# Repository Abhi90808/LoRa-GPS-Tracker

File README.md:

# LoRa GPS Tracker

A custom PCB GPS tracker using LoRa wireless communication for long-range, low-power asset tracking. Designed in KiCad 8, combining a GPS module and LoRa transceiver for remote location reporting.

---

## Features
- LoRa long-range wireless (up to 10km line-of-sight)
- GPS module integration (NEO-6M or compatible)
- Ultra-low power design for battery operation
- SMA or u.FL antenna connector
- Compatible with LoRaWAN / peer-to-peer

## Specifications

| Parameter | Value |
|-----------|-------|
| LoRa Module | Ra-02 / RFM95W (SX1278) |
| GPS Module | NEO-6M / NEO-8M |
| Frequency | 433MHz / 868MHz / 915MHz |
| Range | Up to 10km (line of sight) |
| Supply Voltage | 3.3V |
| Interface | SPI (LoRa), UART (GPS) |
| PCB Layers | 2 |
| Designed With | KiCad 8 |

## Project Structure

```
├── Schematic/       # KiCad schematic (.kicad_sch, PDF)
├── PCB/             # PCB layout (.kicad_pcb, .kicad_pro)
├── Gerbers/         # Fabrication files
├── BOM/             # Bill of materials (CSV)
├── 3D/              # 3D model (.step)
└── Images/          # PCB renders and schematic screenshots
```

## How It Works

The GPS module sends NMEA sentences via UART to the MCU. The MCU parses the latitude/longitude and transmits it as a LoRa packet. A receiver node (another LoRa module or a LoRaWAN gateway) picks up the packet and logs or displays the location.

## Bill of Materials (Summary)

| Component | Value | Qty |
|-----------|-------|-----|
| LoRa Module | Ra-02 / RFM95W | 1 |
| GPS Module | NEO-6M | 1 |
| MCU | ATmega328p / STM32 | 1 |
| Voltage Regulator | AMS1117-3.3V | 1 |
| Antenna Connector | SMA / u.FL | 1 |

## Fabrication

Gerber files are in `/Gerbers`, ready for JLCPCB, PCBWay, or similar.

## License

This project is licensed under the [CERN Open Hardware Licence Version 2 - Strongly Reciprocal (CERN OHL-S v2)](https://ohwr.org/cern_ohl_s_v2.txt).

## Author

**Abhi90808** — [GitHub Profile](https://github.com/Abhi90808)

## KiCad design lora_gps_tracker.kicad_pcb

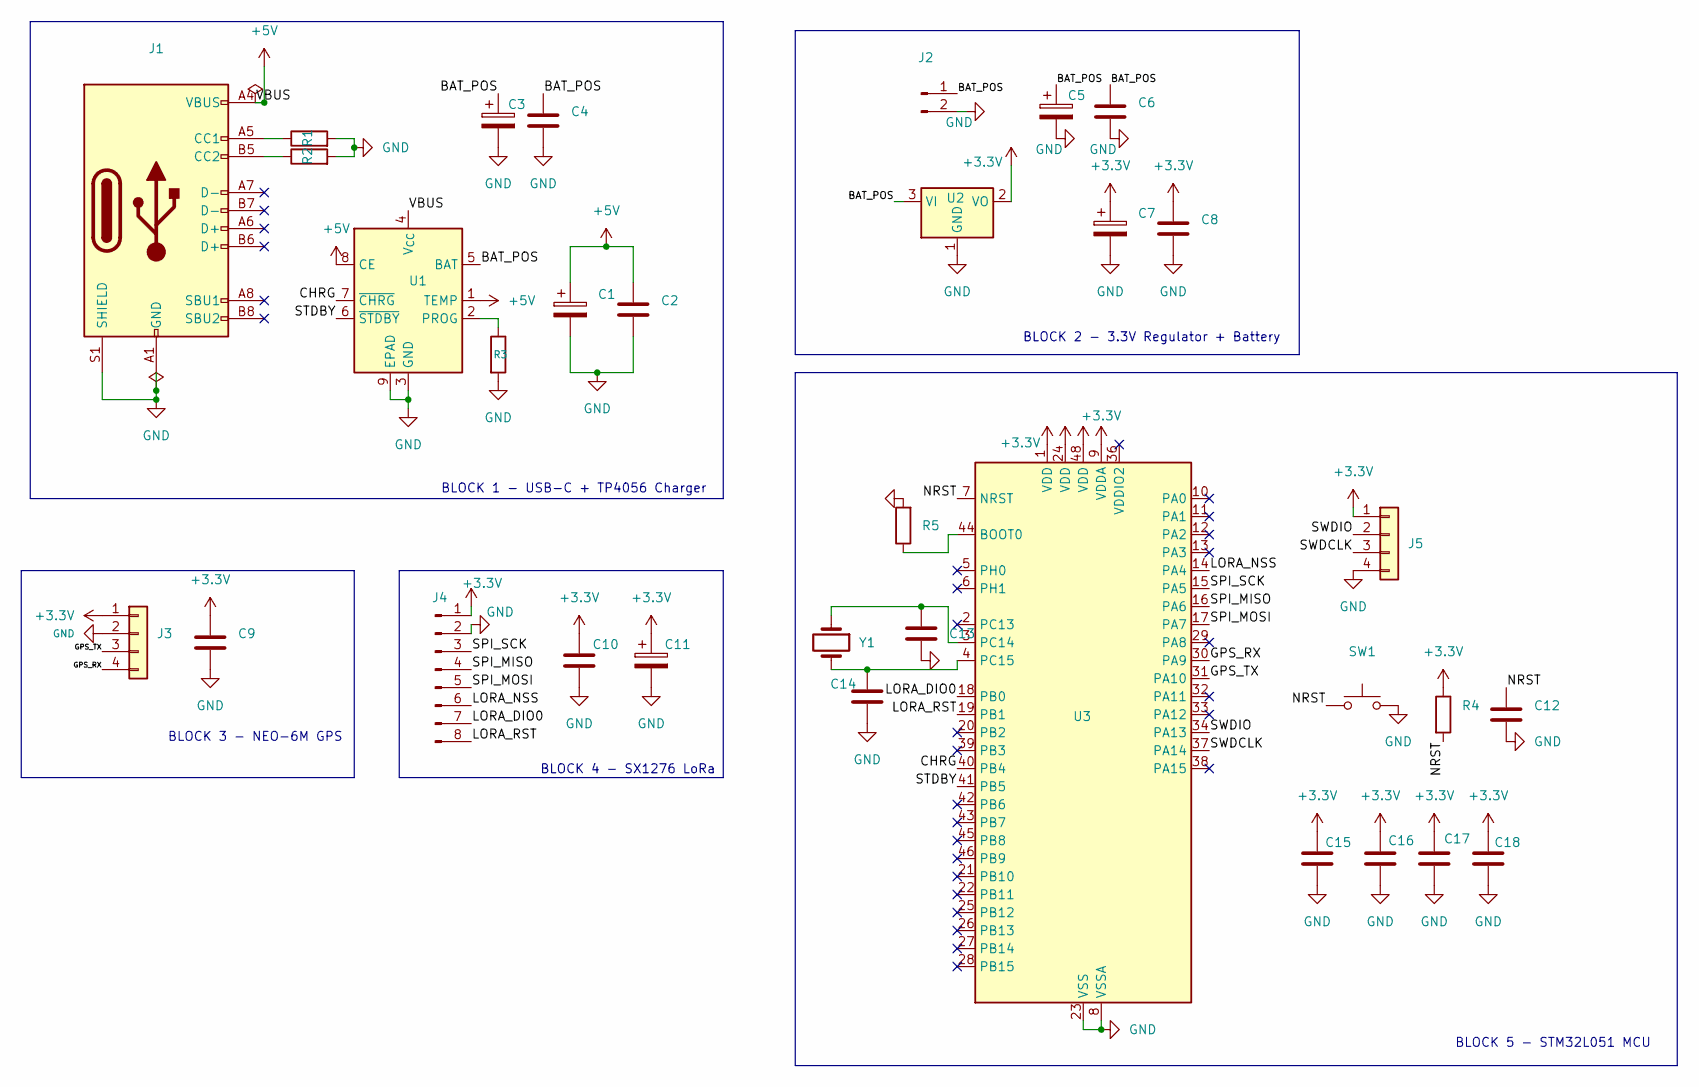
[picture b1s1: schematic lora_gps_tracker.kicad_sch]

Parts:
C1, C3, C5, C7, C11: 10uf; C_0805_2012Metric
C2, C4, C6, C8, C9, C10, C12, C15: 100nf; C_0402_1005Metric
C13, C14, C16, C17, C18: 12pf; C_0402_1005Metric
J1: USB_C; USB_C_Receptacle_XKB_U262-16XN-4BVC11
J2: BATTERY; PinHeader_1x02_P2.54mm_Vertical
J3: NEO6M_GPS; PinHeader_1x04_P2.54mm_Vertical
J4: SX1276_LORA; PinHeader_1x08_P2.54mm_Vertical
J5: SWD_DEBUG; PinHeader_1x04_P2.54mm_Vertical
R1, R2: 5.1k; R_0402_1005Metric
R3: 1.2k; R_0402_1005Metric
R4, R5: 10k; R_0402_1005Metric
SW1: RESET; SW_SPST_B3U-1000P
U1: TP4056; SOIC-8-1EP_3.9x4.9mm_P1.27mm_EP2.41x3.3mm_ThermalVias
U2: AMS1117-3.3; SOT-223-3_TabPin2
U3: STM32L051C8T6; LQFP-48_7x7mm_P0.5mm
Y1: 32.768kHz; Crystal_SMD_3215-2Pin_3.2x1.5mm

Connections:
+3.3V: C7.1, C8.1, C9.1, C10.1, C11.1, C15.1, C16.1, C17.1, C18.1, J3.1, J4.1, J5.1, R4.1, U2.2 (VO), U3.1 (VDD), U3.9 (VDDA), U3.24 (VDD), U3.48 (VDD)
+5V: C1.1, C2.1, J1.A4 (VBUS), J1.A9 (VBUS), J1.B4 (VBUS), J1.B9 (VBUS), U1.1 (TEMP), U1.4 (V_{CC}), U1.8 (CE)
/BAT_POS: C3.1, C4.1, C5.1, C6.1, J2.1, U1.5 (BAT), U2.3 (VI)
/CHRG: U1.7 (~CHRG), U3.40 (PB4)
/GPS_RX: J3.4, U3.30 (PA9)
/GPS_TX: J3.3, U3.31 (PA10)
/LORA_DIO0: J4.7, U3.18 (PB0)
/LORA_NSS: J4.6, U3.14 (PA4)
/LORA_RST: J4.8, U3.19 (PB1)
/NRST: C12.1, R4.2, SW1.1, U3.7 (NRST)
/SPI_MISO: J4.4, U3.16 (PA6)
/SPI_MOSI: J4.5, U3.17 (PA7)
/SPI_SCK: J4.3, U3.15 (PA5)
/STDBY: U1.6 (~STDBY), U3.41 (PB5)
/SWDCLK: J5.3, U3.37 (PA14)
/SWDIO: J5.2, U3.34 (PA13)
GND: C1.2, C2.2, C3.2, C4.2, C5.2, C6.2, C7.2, C8.2, C9.2, C10.2, C11.2, C12.2, C13.1, C14.2, C15.2, C16.2, C17.2, C18.2, J1.A1 (GND), J1.A12 (GND), J1.B1 (GND), J1.B12 (GND), J1.S1 (SHIELD), J2.2, J3.2, J4.2, J5.4, R1.2, R2.2, R3.2, R5.2, SW1.2, U1.3 (GND), U1.9 (EPAD), U2.1 (GND), U3.8 (VSSA), U3.23 (VSS), U3.35 (VSS), U3.47 (VSS)
unnamed: J1.A5 (CC1), R1.1
unnamed: J1.B5 (CC2), R2.1
unnamed: R3.1, U1.2 (PROG)
unnamed: R5.1, U3.44 (BOOT0)
unnamed: C13.2, U3.3 (PC14), Y1.1
unnamed: C14.1, U3.4 (PC15), Y1.2

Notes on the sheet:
BLOCK 3 - NEO-6M GPS
BLOCK 1 - USB-C + TP4056 Charger
BLOCK 4 - SX1276 LoRa
BLOCK 5 - STM32L051 MCU
BLOCK 2 - 3.3V Regulator + Battery

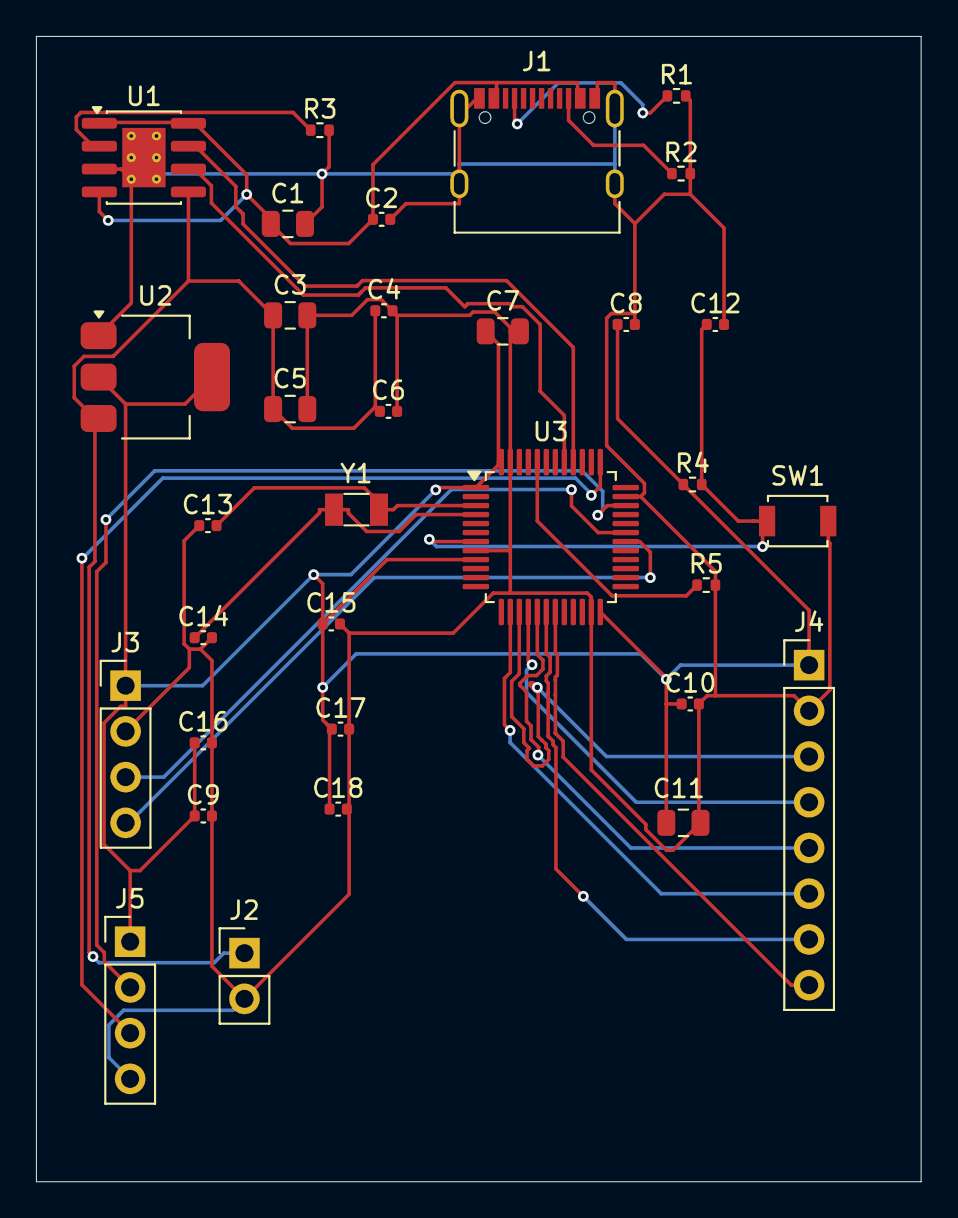
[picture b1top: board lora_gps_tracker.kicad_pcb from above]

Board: 2 copper layers, 49.1 x 63.6 mm, 33 parts (0 on the bottom side), 23 nets.
